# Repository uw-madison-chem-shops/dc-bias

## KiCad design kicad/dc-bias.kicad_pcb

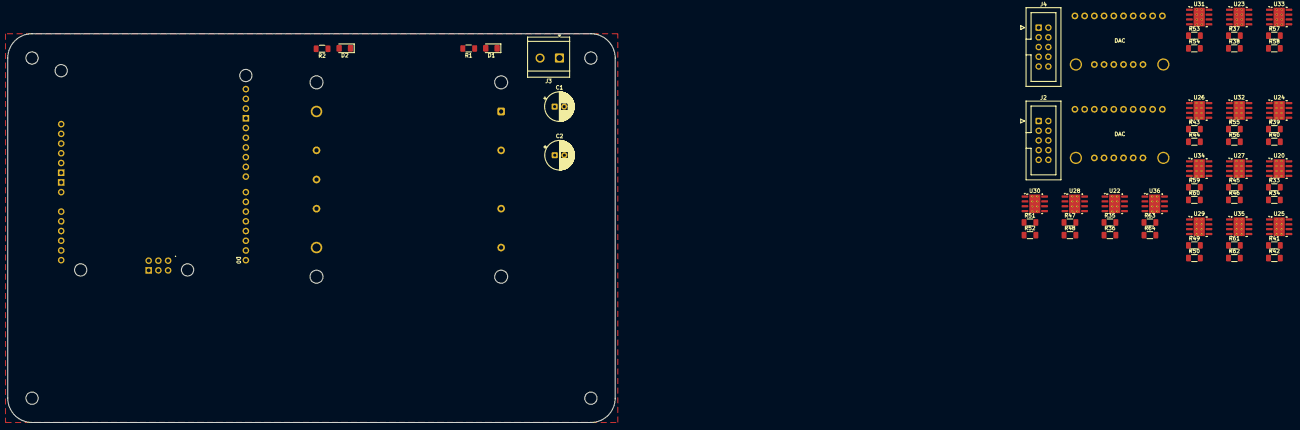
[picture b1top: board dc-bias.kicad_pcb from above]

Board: 2 copper layers, 158.8 x 101.6 mm, 61 parts (1 on the bottom side), 57 nets, no tracks yet.

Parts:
A1: Arduino R4 Minima; Arduino_Uno_R4_Minima_Shield
C1, C2: 100u; CP_Radial_D7.5mm_P2.50mm
D1, D2: LED; LED_1206_3216Metric_Pad1.42x1.75mm_HandSolder
J2, J4: Conn_01x10; IDC-Header_2x05_P2.54mm_Vertical
J3: 24V_IN; TerminalBlock_CUI_TB007-508-02_1x02_P5.08mm_Horizontal
R1, R2: 2k2; R_1206_3216Metric_Pad1.30x1.75mm_HandSolder
R33, R35, R37, R39, R41, R43, R45, R47, R49, R51, R53, R55, R57, R59, R61, R63: 10k; R_1206_3216Metric_Pad1.30x1.75mm_HandSolder
R34, R36, R38, R40, R42, R44, R46, R48, R50, R52, R54, R56, R58, R60, R62, R64: 82k; R_1206_3216Metric_Pad1.30x1.75mm_HandSolder
U17: VHB75W
U19, U21: DAC; adafruitDAC7578
U20, U22, U23, U24, U25, U26, U27, U28, U29, U30, U31, U32, U33, U34, U35, U36: SOIC-8-1EP_3.9x4.9mm_P1.27mm_EP2.95x4.9mm_Mask2.71x3.4mm_Th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

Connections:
+5V: A1.5V1 (5V), U19.16 (VCC), U21.16 (VCC)
+24V: C1.1, J2.10, J3.2, J4.10, R1.1, U17.1 (+V_IN)
+48V: C2.1, R2.1, U17.9 (+V_OUT)
+VDC: U20.7 (V+), U22.7 (V+), U23.7 (V+), U24.7 (V+), U25.7 (V+), U26.7 (V+), U27.7 (V+), U28.7 (V+), U29.7 (V+), U30.7 (V+), U31.7 (V+), U32.7 (V+), U33.7 (V+), U34.7 (V+), U35.7 (V+), U36.7 (V+)
/bias-group1/non-inverting-amplifier-1/IN: U21.2 (0), U22.3 (+)
/bias-group1/non-inverting-amplifier-1/OUT: J4.1, R36.2, U22.6
/bias-group1/non-inverting-amplifier-2/IN: U21.3 (1), U24.3 (+)
/bias-group1/non-inverting-amplifier-2/OUT: J4.2, R40.2, U24.6
/bias-group1/non-inverting-amplifier-3/IN: U21.4 (2), U26.3 (+)
/bias-group1/non-inverting-amplifier-3/OUT: J4.3, R44.2, U26.6
/bias-group1/non-inverting-amplifier-4/IN: U21.5 (3), U28.3 (+)
/bias-group1/non-inverting-amplifier-4/OUT: J4.4, R48.2, U28.6
/bias-group1/non-inverting-amplifier-5/IN: U21.6 (4), U30.3 (+)
/bias-group1/non-inverting-amplifier-5/OUT: J4.5, R52.2, U30.6
/bias-group1/non-inverting-amplifier-6/IN: U21.7 (5), U32.3 (+)
/bias-group1/non-inverting-amplifier-6/OUT: J4.6, R56.2, U32.6
/bias-group1/non-inverting-amplifier-7/IN: U21.8 (6), U34.3 (+)
/bias-group1/non-inverting-amplifier-7/OUT: J4.7, R60.2, U34.6
/bias-group1/non-inverting-amplifier-8/IN: U21.9 (7), U36.3 (+)
/bias-group1/non-inverting-amplifier-8/OUT: J4.8, R64.2, U36.6
/bias-group-1/non-inverting-amplifier-1/IN: U19.2 (0), U20.3 (+)
/bias-group-1/non-inverting-amplifier-1/OUT: J2.1, R34.2, U20.6
/bias-group-1/non-inverting-amplifier-2/IN: U19.3 (1), U23.3 (+)
/bias-group-1/non-inverting-amplifier-2/OUT: J2.2, R38.2, U23.6
/bias-group-1/non-inverting-amplifier-3/IN: U19.4 (2), U25.3 (+)
/bias-group-1/non-inverting-amplifier-3/OUT: J2.3, R42.2, U25.6
/bias-group-1/non-inverting-amplifier-4/IN: U19.5 (3), U27.3 (+)
/bias-group-1/non-inverting-amplifier-4/OUT: J2.4, R46.2, U27.6
/bias-group-1/non-inverting-amplifier-5/IN: U19.6 (4), U29.3 (+)
/bias-group-1/non-inverting-amplifier-5/OUT: J2.5, R50.2, U29.6
/bias-group-1/non-inverting-amplifier-6/IN: U19.7 (5), U31.3 (+)
/bias-group-1/non-inverting-amplifier-6/OUT: J2.6, R54.2, U31.6
/bias-group-1/non-inverting-amplifier-7/IN: U19.8 (6), U33.3 (+)
/bias-group-1/non-inverting-amplifier-7/OUT: J2.7, R58.2, U33.6
/bias-group-1/non-inverting-amplifier-8/IN: U19.9 (7), U35.3 (+)
/bias-group-1/non-inverting-amplifier-8/OUT: J2.8, R62.2, U35.6
GND: A1.GND1 (GND), A1.GND2 (GND), A1.GND3 (GND), A1.GND4 (SPI_GND), C1.2, C2.2, D1.1 (K), D2.1 (K), J2.9, J3.1, J4.9, R33.2, R35.2, R37.2, R39.2, R41.2, R43.2, R45.2, R47.2, R49.2, R51.2, R53.2, R55.2, R57.2, R59.2, R61.2, R63.2, U17.3 (CASE), U17.4 (-V_IN), U17.5 (-V_OUT), U19.10 (GND), U19.15 (GND), U20.4 (V-), U21.10 (GND), U21.15 (GND), U22.4 (V-), U23.4 (V-), U24.4 (V-), U25.4 (V-), U26.4 (V-), U27.4 (V-), U28.4 (V-), U29.4 (V-), U30.4 (V-), U31.4 (V-), U32.4 (V-), U33.4 (V-), U34.4 (V-), U35.4 (V-), U36.4 (V-)
unnamed: D1.2 (A), R1.2
unnamed: D2.2 (A), R2.2
unnamed: R33.1, R34.1, U20.2 (-)
unnamed: R35.1, R36.1, U22.2 (-)
unnamed: R37.1, R38.1, U23.2 (-)
unnamed: R39.1, R40.1, U24.2 (-)
unnamed: R41.1, R42.1, U25.2 (-)
unnamed: R43.1, R44.1, U26.2 (-)
unnamed: R45.1, R46.1, U27.2 (-)
unnamed: R47.1, R48.1, U28.2 (-)
unnamed: R49.1, R50.1, U29.2 (-)
unnamed: R51.1, R52.1, U30.2 (-)
unnamed: R53.1, R54.1, U31.2 (-)
unnamed: R55.1, R56.1, U32.2 (-)
unnamed: R57.1, R58.1, U33.2 (-)
unnamed: R59.1, R60.1, U34.2 (-)
unnamed: R61.1, R62.1, U35.2 (-)
unnamed: R63.1, R64.1, U36.2 (-)
SCL: A1.SCL, U19.14 (SCL), U21.14 (SCL)
SDA: A1.SDA, U19.13 (SDA), U21.13 (SDA)
